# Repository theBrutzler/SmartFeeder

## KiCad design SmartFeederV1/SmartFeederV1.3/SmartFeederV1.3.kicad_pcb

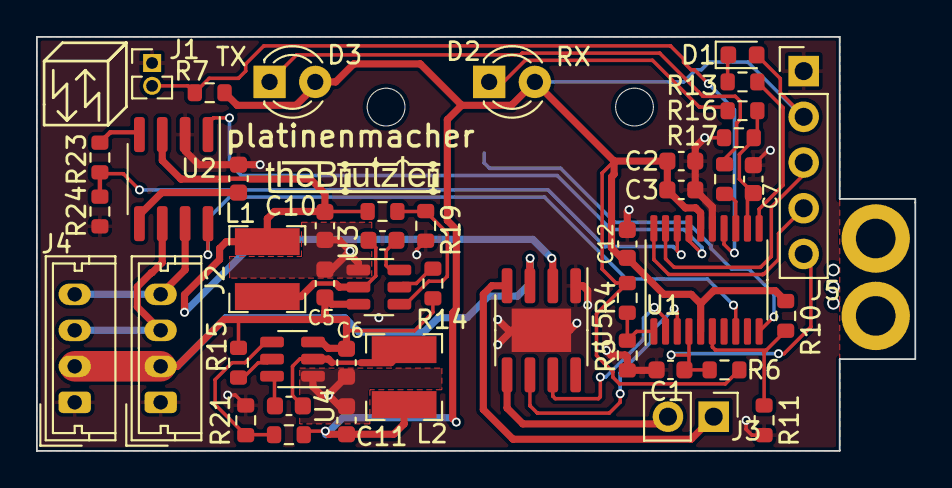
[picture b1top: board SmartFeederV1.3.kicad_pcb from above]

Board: 4 copper layers, 48.8 x 23.0 mm, 49 parts (1 on the bottom side), 34 nets.

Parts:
C1, C3, C4, C7, C8, C9, C12: 100nF; C_0603_1608Metric
C2: 4,7µF; C_0603_1608Metric
C5, C6, C10, C11: 4µ7; C_0603_1608Metric
D1: LED; LED_0603_1608Metric
D2: D_Photo; LED_D3.0mm_IRBlack
D3: IR204A; LED_D3.0mm_IRBlack
H1, H2: MountingHole_Pad; MountingHole_2.2mm_M2_DIN965_Pad
J1: Conn_01x02_Female; PinHeader_1x02_P1.27mm_Vertical
J2, J4: Conn_01x04_Female; Molex_Micro-Latch_53253-0470_1x04_P2.00mm_Vertical
J3: Conn_01x02_Female; PinHeader_1x02_P2.54mm_Vertical
J5: Conn_01x05_Female; PinHeader_1x05_P2.54mm_Vertical
L1, L2: 10µ; L_Bourns-SRN4018
R4, R5, R22: 100; R_0603_1608Metric
R6, R7, R10, R11, R14, R15, R17: 4K7; R_0603_1608Metric
R13, R16, R23: 1K; R_0603_1608Metric
R18: 733K; R_0603_1608Metric
R19, R21: 100K; R_0603_1608Metric
R20: 450K; R_0603_1608Metric
R24: 2K; R_0603_1608Metric
SM3, SM3#2: SYM_Arrow45_Tiny; Symbol_kurzschlussblog
U1: STM32F070F6; TSSOP-20_4.4x6.5mm_P0.65mm
U2: SN65HVD1050D; SOIC-8_3.9x4.9mm_P1.27mm
U3, U4: TPS54202DDC; SOT-23-6
U5: BDR6133; SOIC-8-1EP_3.9x4.9mm_P1.27mm_EP2.41x3.3mm

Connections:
+3V3: C2.2, C3.2, C11.1, C12.2, D1.2 (A), D2.2 (A), D3.2 (A), J5.2, L2.2, R4.1, R6.1, R7.1, R10.1, R20.2, U1.5 (VDDA), U1.16 (VDD)
/HEAT: C5.1, C6.1, C10.1, H1.1, H2.1, J2.2, J4.2, L1.2, R14.2, R15.2, R18.2, U2.3 (VCC), U3.3 (VIN), U4.3 (VIN), U5.2 (VDD), U5.3 (VM)
/OW: J1.2, R7.2, U1.14 (PB1)
/PA2: U1.8 (PA2), U2.8 (S)
/PF0: U1.2 (PF0), U5.7 (INB)
/PF1: U1.3 (PF1), U5.6 (INA)
/RST: C1.1, J5.5, R6.2, U1.4 (NRST)
/SWCLK: J5.4, U1.20 (PA14)
/SWDIO: J5.3, U1.19 (PA13)
/UART1_RX: R23.2, R24.1, U1.18 (PA10)
/UART1_TX: U1.17 (PA9), U2.1 (TXD)
GND: C1.2, C2.1, C3.1, C4.2, C5.2, C6.2, C7.2, C10.2, C11.2, C12.1, J1.1, J2.1, J4.1, J5.1, R5.2, R11.2, R17.2, R19.1, R21.1, R24.2, U1.15 (VSS), U2.2 (GND), U3.1 (GND), U4.1 (GND), U5.1 (GND), U5.9 (GND)
unnamed: D1.1 (K), R13.1
unnamed: D2.1 (K), R16.1
unnamed: D3.1 (K), R22.1
unnamed: J2.3, J4.3, U2.6 (CANL)
unnamed: J2.4, J4.4, U2.7 (CANH)
unnamed: J3.1, U5.4 (OUTA)
unnamed: J3.2, U5.5 (OUTB)
unnamed: R4.2, R5.1, U1.1 (BOOT0)
unnamed: R10.2, R11.1, U1.6 (PA0)
unnamed: R13.2, U1.11 (PA5)
unnamed: C7.1, R16.2, R17.1, U1.12 (PA6)
unnamed: R22.2, U1.13 (PA7)
unnamed: R23.1, U2.4 (RXD)
unnamed: C4.1, U2.5 (VREF)
unnamed: C8.1, U3.6 (BOOT)
unnamed: R14.1, U3.5 (EN)
unnamed: R18.1, R19.2, U3.4 (FB)
unnamed: C8.2, L1.1, U3.2 (SW)
unnamed: C9.1, U4.6 (BOOT)
unnamed: R15.1, U4.5 (EN)
unnamed: R20.1, R21.2, U4.4 (FB)
unnamed: C9.2, L2.1, U4.2 (SW)

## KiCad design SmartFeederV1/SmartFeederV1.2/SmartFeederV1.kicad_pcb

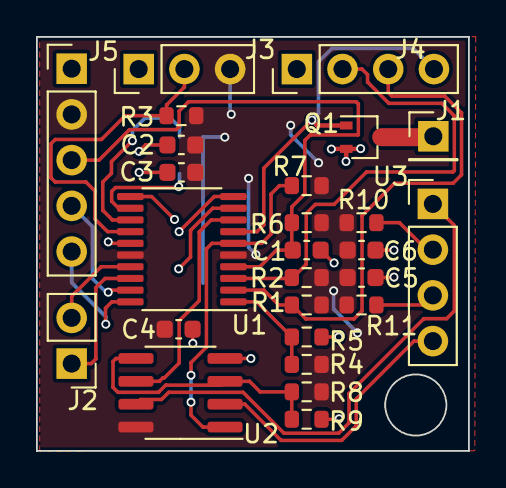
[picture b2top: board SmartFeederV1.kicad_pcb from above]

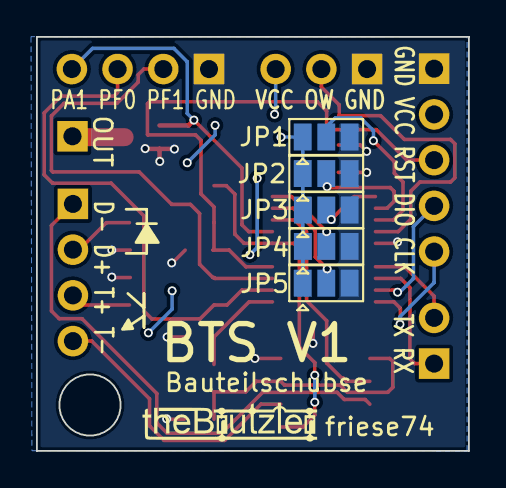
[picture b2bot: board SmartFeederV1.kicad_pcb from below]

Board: 2 copper layers, 24.0 x 23.0 mm, 31 parts (5 on the bottom side), 25 nets.

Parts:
C1, C3, C4, C5, C6: 100nF; C_0603_1608Metric
C2: 4,7µF; C_0603_1608Metric
J1: Conn_01x01_Female; PinHeader_1x01_P2.54mm_Vertical
J2: Conn_01x02_Female; PinHeader_1x02_P2.54mm_Vertical
J3: Conn_01x03_Female; PinHeader_1x03_P2.54mm_Vertical
J4: Conn_01x04_Female; PinHeader_1x04_P2.54mm_Vertical
J5: Conn_01x05_Female; PinHeader_1x05_P2.54mm_Vertical
JP1, JP2, JP3, JP4, JP5: SolderJumper_3_Open; SolderJumper-3_P1.3mm_Open_Pad1.0x1.5mm
Q1: CJ2102; SOT-323_SC-70
R1, R2, R6, R7, R8, R9: 4K7; R_0603_1608Metric
R3, R4, R5: 2K; R_0603_1608Metric
R10, R11: 100R; R_0603_1608Metric
U1: STM32F030F4Px; TSSOP-20_4.4x6.5mm_P0.65mm
U2: LM393; SOIC-8_3.9x4.9mm_P1.27mm
U3: ITR1100; PinHeader_1x04_P2.54mm_Vertical

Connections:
/ADC_IN0: R7.2, U1.6 (PA0), U2.1
/OW: J3.2, R3.2, U1.14 (PB1)
/PA1: J4.4, Q1.1 (G), U1.7 (PA1)
/PF0: J4.3, R1.2, U1.2 (PF0)
/PF1: J4.2, R2.2, U1.3 (PF1)
/RST: C1.1, J5.3, R6.2, U1.4 (NRST)
/SWCLK: J5.5, U1.20 (PA14)
/SWDIO: J5.4, U1.19 (PA13)
/TIM15_CH1: U1.8 (PA2), U2.6 (_)
/UART1_RX: J2.1, U1.18 (PA10)
/UART1_TX: J2.2, U1.17 (PA9)
GND: C1.2, C2.1, C3.1, C4.2, C5.2, C6.2, J3.1, J4.1, J5.1, JP1.3 (B), JP2.3 (B), JP3.3 (B), JP4.3 (B), JP5.3 (B), Q1.2 (S), R5.2, R9.2, U1.15 (VSS), U2.4 (V-)
unnamed: J1.1, Q1.3 (D)
unnamed: JP1.2 (C), U1.13 (PA7)
unnamed: JP2.2 (C), U1.12 (PA6)
unnamed: JP3.2 (C), U1.11 (PA5)
unnamed: JP4.2 (C), U1.10 (PA4)
unnamed: JP5.2 (C), U1.9 (PA3)
unnamed: R4.2, R5.1, U1.1 (BOOT0)
unnamed: R8.2, R9.1, U2.3 (+), U2.5 (+)
unnamed: R10.2, U3.2 (A)
unnamed: R11.2, U3.3 (C)
unnamed: U2.2 (-), U3.4 (E)
unnamed: U2.7, U3.1 (K)
VCC: C2.2, C3.2, C4.1, C5.1, C6.1, J3.3, J5.2, JP1.1 (A), JP2.1 (A), JP3.1 (A), JP4.1 (A), JP5.1 (A), R1.1, R2.1, R3.1, R4.1, R6.1, R7.1, R8.1, R10.1, R11.1, U1.5 (VDDA), U1.16 (VDD), U2.8 (V+)

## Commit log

2023-01-18 Initial Upload
